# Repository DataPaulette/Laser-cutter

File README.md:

# Laser-cutter
## Electronic for Arduino & GRBL

GRBL : https://github.com/gnea/grbl
DataPaulette wiki page : http://wiki.datapaulette.org/doku.php/atelier/documentation/outillage/laser

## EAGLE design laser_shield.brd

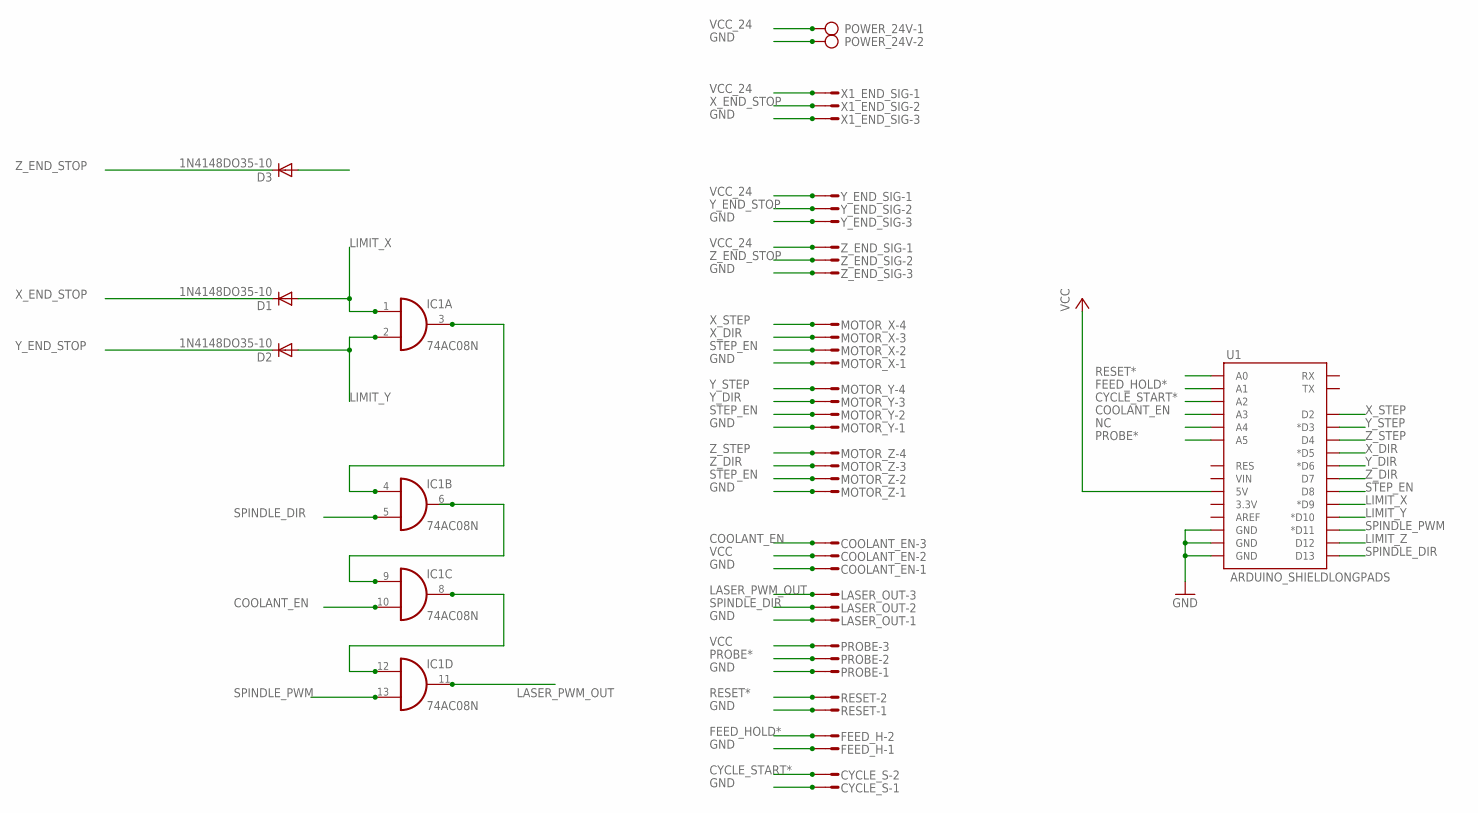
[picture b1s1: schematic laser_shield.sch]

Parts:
COOLANT_EN: L03P
CYCLE_S: L02P
D1, D2, D3: 1N4148DO35-10; DO35-10
FEED_H: L02P
IC1: 74AC08N; DIL14
LASER_OUT: L03P
MOTOR_X: L04P
MOTOR_Y: L04P
MOTOR_Z: L04P
POWER_24V: AK300/2
PROBE: L03P
RESET: L02P
U1: ARDUINO_SHIELDLONGPADS; DUEMILANOVE_SHIELD_LONGPADS
X1_END_SIG: L03P
Y_END_SIG: L03P
Z_END_SIG: L03P

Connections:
COOLANT_EN: COOLANT_EN.3, IC1.10 (I1), U1.A3
CYCLE_START*: CYCLE_S.2, U1.A2
FEED_HOLD*: FEED_H.2, U1.A1
GND: COOLANT_EN.1, CYCLE_S.1, FEED_H.1, IC1.7 (GND), LASER_OUT.1, MOTOR_X.1, MOTOR_Y.1, MOTOR_Z.1, POWER_24V.2, PROBE.1, RESET.1, U1.GND@0 (GND), U1.GND@1 (GND), U1.GND@2 (GND), X1_END_SIG.3, Y_END_SIG.3, Z_END_SIG.3
LASER_PWM_OUT: IC1.11 (O), LASER_OUT.3
LIMIT_X: D1.A, IC1.1 (I0), U1.D9 (*D9)
LIMIT_Y: D2.A, IC1.2 (I1), U1.D10 (*D10)
LIMIT_Z: D3.A, U1.D12
unnamed: IC1.3 (O), IC1.4 (I0)
unnamed: IC1.6 (O), IC1.9 (I0)
unnamed: IC1.8 (O), IC1.12 (I0)
NC: U1.A4
PROBE*: PROBE.2, U1.A5
RESET*: RESET.2, U1.A0
SPINDLE_DIR: IC1.5 (I1), LASER_OUT.2, U1.D13
SPINDLE_PWM: IC1.13 (I1), U1.D11 (*D11)
STEP_EN: MOTOR_X.2, MOTOR_Y.2, MOTOR_Z.2, U1.D8
VCC: COOLANT_EN.2, IC1.14 (VCC), PROBE.3, U1.5V
VCC_24: POWER_24V.1, X1_END_SIG.1, Y_END_SIG.1, Z_END_SIG.1
X_DIR: MOTOR_X.3, U1.D5 (*D5)
X_END_STOP: D1.C, X1_END_SIG.2
X_STEP: MOTOR_X.4, U1.D2
Y_DIR: MOTOR_Y.3, U1.D6 (*D6)
Y_END_STOP: D2.C, Y_END_SIG.2
Y_STEP: MOTOR_Y.4, U1.D3 (*D3)
Z_DIR: MOTOR_Z.3, U1.D7
Z_END_STOP: D3.C, Z_END_SIG.2
Z_STEP: MOTOR_Z.4, U1.D4

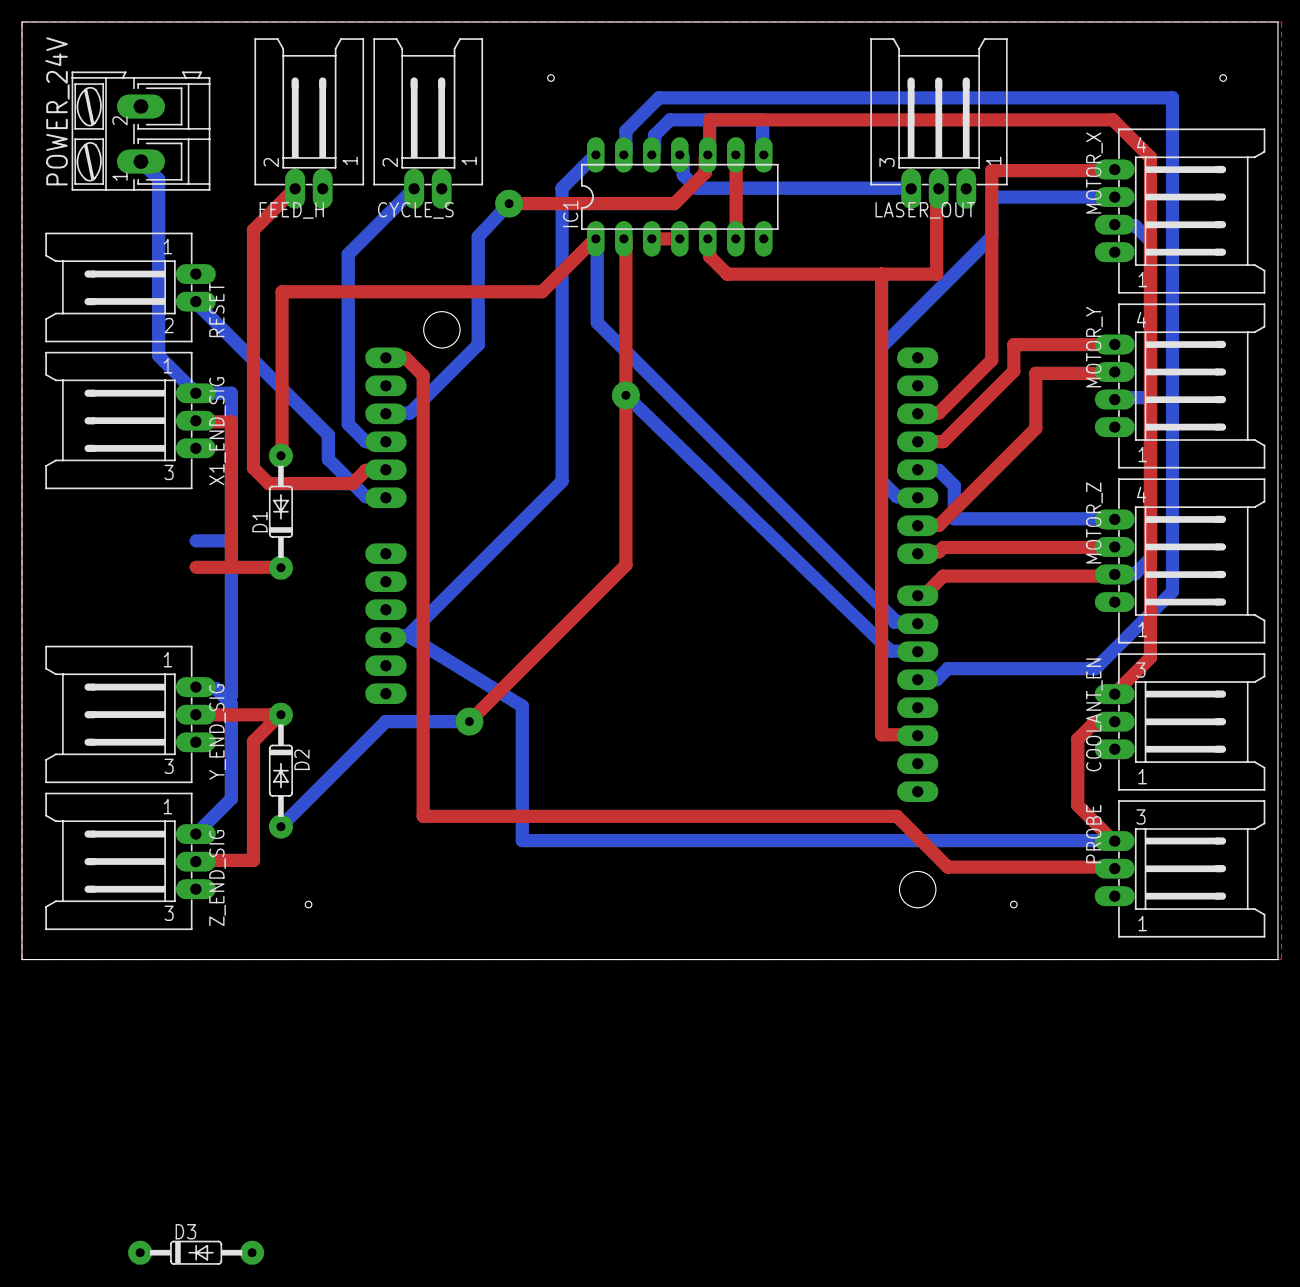
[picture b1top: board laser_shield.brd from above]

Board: 2 copper layers, 114.0 x 85.1 mm, 18 parts (1 on the bottom side), 27 nets.

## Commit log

2017-01-30 Modified for regular GRBL
2017-01-30 Added PDF to print
2017-01-31 Added links
2017-01-31 Added new connectors
2017-01-31 New rooting
2017-01-31 Added .pdf top & bottom PCB
2017-01-31 Added Z_LIMIT

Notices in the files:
parts and their libraries:
SparkFun-Boards: Licensing: Creative Commons ShareAlike 4.0 International - https://creativecommons.org/licenses/by-sa/4.0
